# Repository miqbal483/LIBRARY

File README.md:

SISTEM PENGINGAT WAKTU KUNJUNGAN PUSTAKA AKAN SEGERA BERAKHIR 

Short Video Iklan:
https://youtu.be/MK6m6q8eAms?si=uDOMp7hHmW7Q7evs

Project Presentation:
https://youtu.be/26DVSYQhU48?si=dGXOXOYlQXr6ws6L

Simulation Project:
https://wokwi.com/projects/399544200636423169

Simulation Video:
https://youtu.be/jXPkd2OSdCM

3D Design in Tinkercad:
https://www.tinkercad.com/things/8WcROYUEPT0-smooth-maimu/edit?sharecode=sExdqkGP5Q3-d2moFkXHQfWHruUjbhXInHOObu-gGvI

Thingiverse Available!
https://www.thingiverse.com/thing:6656032

## TABEL OF CONTENT
- [Deskripsi](#Deskripsi)
- [Meet out team](#Meet-our-team)
- [Sistem ](#Sistem)
  - [Flowchart](#Flowchart)
  - [Cara Kerja](#Cara-Kerja)
- [Komponen dan Software](#Komponen-dan-Software)
  - [Komponen](#Komponen)
  - [Software](#Software)
- [Detail Proyek](#Detail-Proyek)
  - [PCB](#PCB)
    - [Desain Skematik PCB](#Desain-Skematik-PCB)
    - [Desain Brd PCB](#Desain-Brd-PCB)
    - [Vidio Desain PCB](#Vidio-Desain-PCB)
  - [3D Kemasan Proyek](#3D-Kemasan-Proyek)
    - [Desain 3D ](#Desain-3D-Case-Arduino)
          -[Desain tampak atas](#Desain-tampak-atas)
          -[Desain tampak samping](#Desain-tampak-samping) 
    - [Video Pembuatan Desain 3D](#Video-Pembuatan-Desain-3D)
  
  - [Program](#Program)
    - [Convert Audio](#Convert-Audio)
    - [Video Convert Audio](#Video-Convert-Audio)
    - [Simulasi Program](#Simulasi-Program)
    - [Video Simulasi](#Video-Simulasi)
    - [Realisasi Program](#Realisasi-Program)
- [Dokumentasi Proyek dan Team](#Dokumentasi-Proyek-dan-Team)
________________________________________________________________________________________________________________________________________________________________________________________________________________________________________________________
## Deskripsi 
    Smart alarm library adalah perpustakaan yang di rancang khusus untuk meningkatkan pengalaman pengunjung. 
  Perpustakan dengan  integrasi teknologi alarm cerdas dengan sistem alarm pintar yang membantu pengguna untuk mengatur 
  waktu belajar, membaca, dan aktivitas lainnya Dengan teknologi ini, pengguna dapat memaksimalkan waktu mereka di 
  perpustakaan, memastikan kenyamanan dan produktivitas yang lebih tinggi dalam proses belajar dan penelitian.

## Meet out team

## SISTEM   
-Flowchart
-Cara kerja 

## Komponent Dan Software
Tabel Komponen
| No.  | Nama Barang  | Jumlah  |
| :------------: | :------------: | :------------: |
| 1  | Arduino mega 2560  |  |
| 2  |  Switch  |  |
| 3  |  Speaker |   |
| 4  |  Amplyfier 5V |  |
| 5  |  Resistor 330k Ohm |  |
| 6  |  Led |  |
| 7  |  Button |  |

Software
| No.  | Nama Software  | Gambar  |
| :------------: | :------------: | :------------: |
| 1  | Git Hub  |  |
| 2  |  Visual studio 2022  |  |

## DETILE PROJECT
1.PCB
-Desain Skematik PCB

-Desain Brd PCB

-Vidio Desain PCB

https://youtu.be/Cwl16uaGwfU?si=vJ_uzfdw53V6q0ss

3D-K
## Kemasan-Proyek
-3D Desain
   -tampak atas 

   -tampak samping   

-Vidio Pembuatan 3D desain
 find it on youtube  :https://youtu.be/gMB6TkZ90Xk?si=3x84PS4rwlSPPd9r

## Dokumentasi Proyek dan Team

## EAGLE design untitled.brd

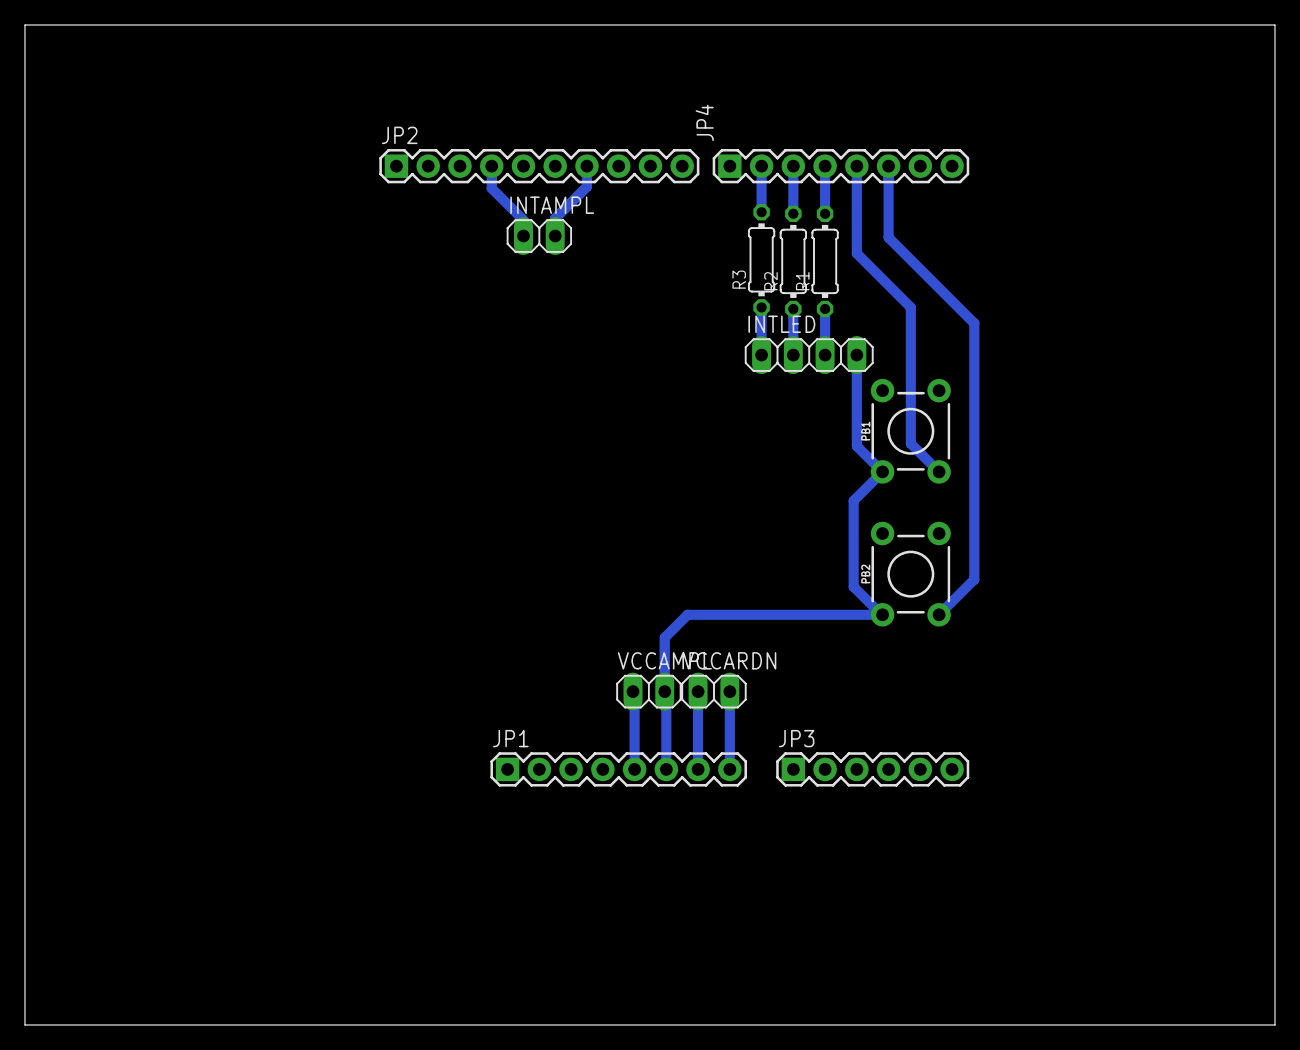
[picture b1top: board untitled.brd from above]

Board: 2 copper layers, 100.0 x 80.0 mm, 13 parts (0 on the bottom side), 14 nets.

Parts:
INTAMPL: 1X02
INTLED: 1X04
JP1, JP4: CONN-1X08
JP2: ARDUINO_CONN-IO_HSIP; CONN-1X10
JP3: CONN-1X06
PB1, PB2: TACTILE_SWITCH_PTH_6.0MM
R1, R2, R3: 0204/7
VCCAMPL: 1X02
VCCARDN: 1X02

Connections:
unnamed: INTAMPL.2, JP2.7
unnamed: INTAMPL.1, JP2.4
unnamed: JP1.8, VCCARDN.2
unnamed: JP1.7, VCCARDN.1
unnamed: INTLED.4, JP1.6, PB1.1, PB2.1, VCCAMPL.2
unnamed: JP1.5, VCCAMPL.1
unnamed: JP4.5, PB1.3
unnamed: JP4.6, PB2.3
unnamed: JP4.2, R3.2
unnamed: INTLED.2, R2.1
unnamed: INTLED.3, R1.1
unnamed: JP4.4, R1.2
unnamed: JP4.3, R2.2
unnamed: INTLED.1, R3.1

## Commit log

2024-05-06 README.md
2024-05-06 Desain not final yet
2024-05-06 circuit bord and scematich
2024-05-13 Create DOKUMENTASI
2024-05-13 menambahkan link simulasi pada README.md
2024-05-13 3D Mock Up
2024-05-13 Update desain 3D
2024-05-13 Progress Desain
2024-05-13 Progress Desain 3D
2024-05-19 Create PROGRAMING
2024-05-19 Update PROGRAMING
2024-05-19 Rename Screenshot 2024-05-13 103920.png to Proses Disain 3D
2024-05-20 Menamahkan Proposal
2024-06-09 sheild arduino
    schematic and board
2024-06-10 Update video link
2024-06-10 design sheild arduino
    schematic and board

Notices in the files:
parts and their libraries:
SparkFun-Switches: Licensing: Creative Commons ShareAlike 4.0 International - https://creativecommons.org/licenses/by-sa/4.0
